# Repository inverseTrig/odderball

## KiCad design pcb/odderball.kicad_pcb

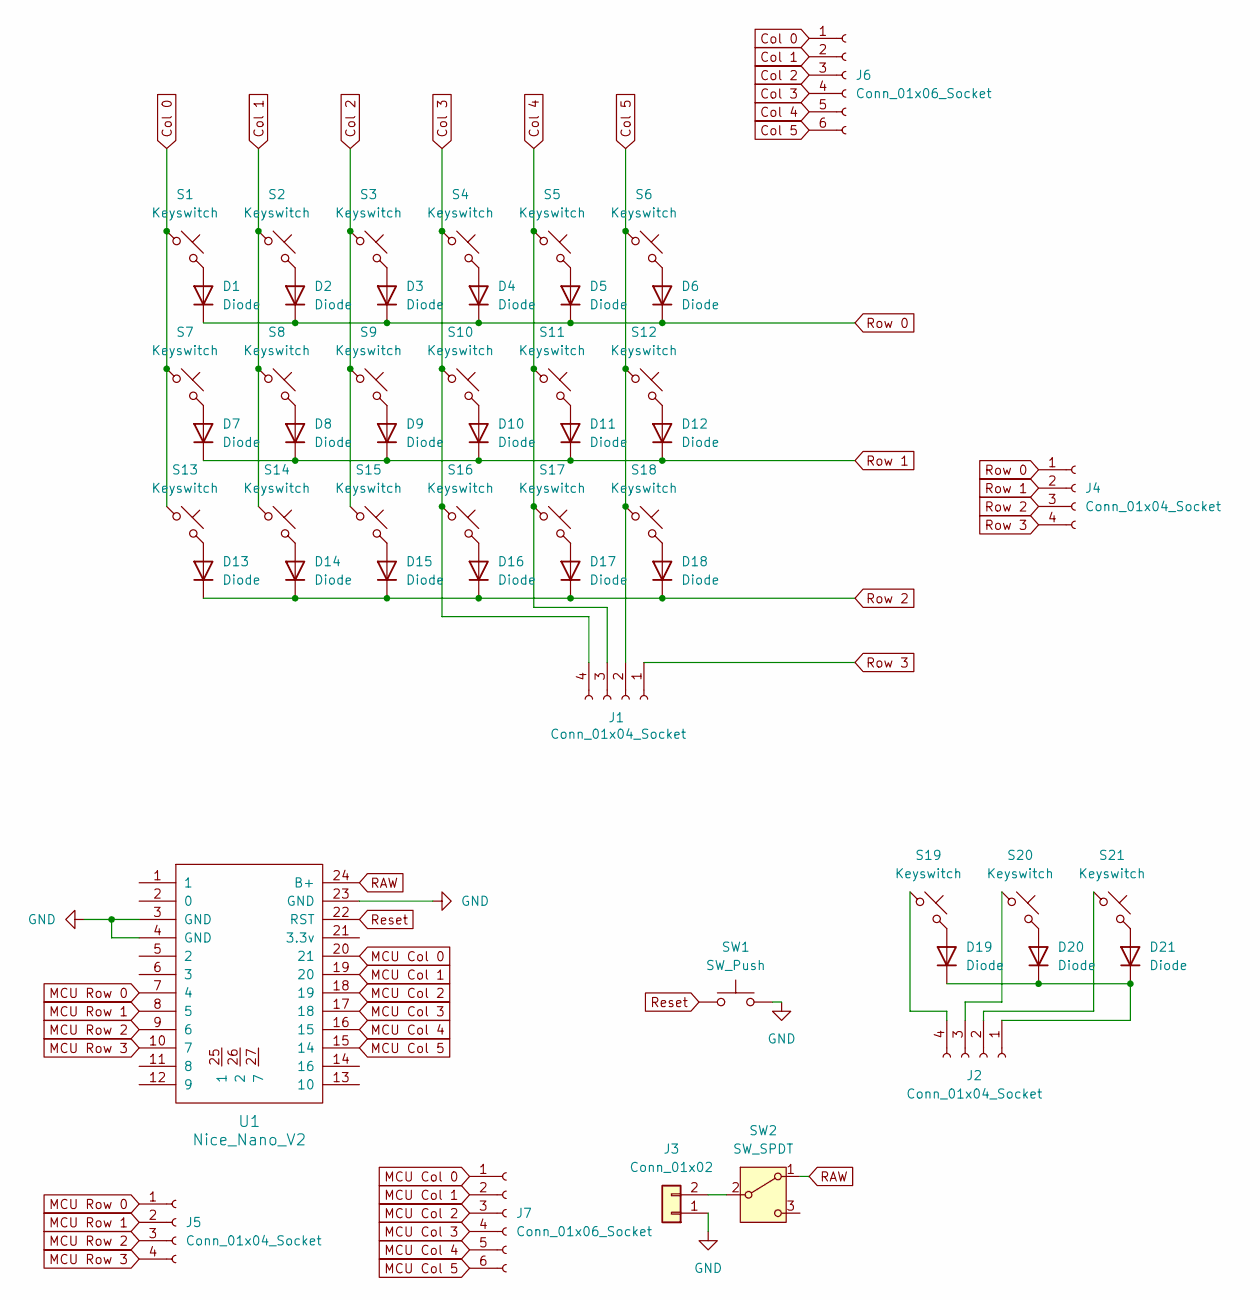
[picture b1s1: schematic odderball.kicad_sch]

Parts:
D1, D2, D3, D4, D5, D6, D7, D8, D9, D10, D11, D12, D13, D14, D15, D16, D17, D18, D19, D20, D21: Diode; Diode_TH_SOD123
J1, J2, J4, J5: Conn_01x04_Socket; PinSocket_1x04_P2.54mm_Vertical
J3: Conn_01x02; JST_PH_S2B-PH-SM4-TB_1x02-1MP_P2.00mm_Horizontal
J6, J7: Conn_01x06_Socket; PinSocket_1x06_P2.54mm_Vertical
S1, S2, S3, S4, S5, S6, S7, S8, S9, S10, S11, S12, S13, S14, S15, S16, S17, S18, S19, S20, S21: Keyswitch; MX_Solder_1.00u_Reversible
SW1: SW_Push; alps_sksn
SW2: SW_SPDT; switch_SSSS811101
U1: Nice_Nano_V2

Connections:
Col 0: J6.1, S1.1, S7.1, S13.1
Col 1: J6.2, S2.1, S8.1, S14.1
Col 2: J6.3, S3.1, S9.1, S15.1
Col 3: J1.4, J6.4, S4.1, S10.1, S16.1
Col 4: J1.3, J6.5, S5.1, S11.1, S17.1
Col 5: J1.2, J6.6, S6.1, S12.1, S18.1
GND: J3.1, SW1.2, U1.3 (GND), U1.4 (GND), U1.23 (GND)
MCU Col 0: J7.1, U1.20 (21)
MCU Col 1: J7.2, U1.19 (20)
MCU Col 2: J7.3, U1.18 (19)
MCU Col 3: J7.4, U1.17 (18)
MCU Col 4: J7.5, U1.16 (15)
MCU Col 5: J7.6, U1.15 (14)
MCU Row 0: J5.1, U1.7 (4)
MCU Row 1: J5.2, U1.8 (5)
MCU Row 2: J5.3, U1.9 (6)
MCU Row 3: J5.4, U1.10 (7)
unnamed: D1.2 (A), S1.2
unnamed: D2.2 (A), S2.2
unnamed: D3.2 (A), S3.2
unnamed: D4.2 (A), S4.2
unnamed: D5.2 (A), S5.2
unnamed: D6.2 (A), S6.2
unnamed: D7.2 (A), S7.2
unnamed: D8.2 (A), S8.2
unnamed: D9.2 (A), S9.2
unnamed: D10.2 (A), S10.2
unnamed: D11.2 (A), S11.2
unnamed: D12.2 (A), S12.2
unnamed: D13.2 (A), S13.2
unnamed: D14.2 (A), S14.2
unnamed: D15.2 (A), S15.2
unnamed: D16.2 (A), S16.2
unnamed: D17.2 (A), S17.2
unnamed: D18.2 (A), S18.2
unnamed: D19.2 (A), S19.2
unnamed: D19.1 (K), D20.1 (K), D21.1 (K), J2.1
unnamed: D20.2 (A), S20.2
unnamed: D21.2 (A), S21.2
unnamed: J2.2, S21.1
unnamed: J2.3, S20.1
unnamed: J2.4, S19.1
unnamed: J3.2, SW2.2 (B)
RAW: SW2.1 (A), U1.24 (B+)
Reset: SW1.1, U1.22 (RST)
Row 0: D1.1 (K), D2.1 (K), D3.1 (K), D4.1 (K), D5.1 (K), D6.1 (K), J4.1
Row 1: D7.1 (K), D8.1 (K), D9.1 (K), D10.1 (K), D11.1 (K), D12.1 (K), J4.2
Row 2: D13.1 (K), D14.1 (K), D15.1 (K), D16.1 (K), D17.1 (K), D18.1 (K), J4.3
Row 3: J1.1, J4.4

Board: 2 copper layers, 52 parts (21 on the bottom side), 49 nets, no tracks yet.

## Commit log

2024-07-26 feat: add extra thumb key; add more bolt holes for support; change thumb keys to 1u
2024-07-26 feat: remove trrs
2024-07-27 chore: add ds_store to gitignore
2024-08-10 feat: adding temporary pcb files, plate and pcb dxf related files; modifying case to use screw inserts
2024-08-11 feat: adding pmw3610 cover
2024-08-11 fix: cable cutout between thumb and pcb
2024-08-11 fix: add slight height to pmw3610 feet
2024-08-11 wip: adding mcuholder
